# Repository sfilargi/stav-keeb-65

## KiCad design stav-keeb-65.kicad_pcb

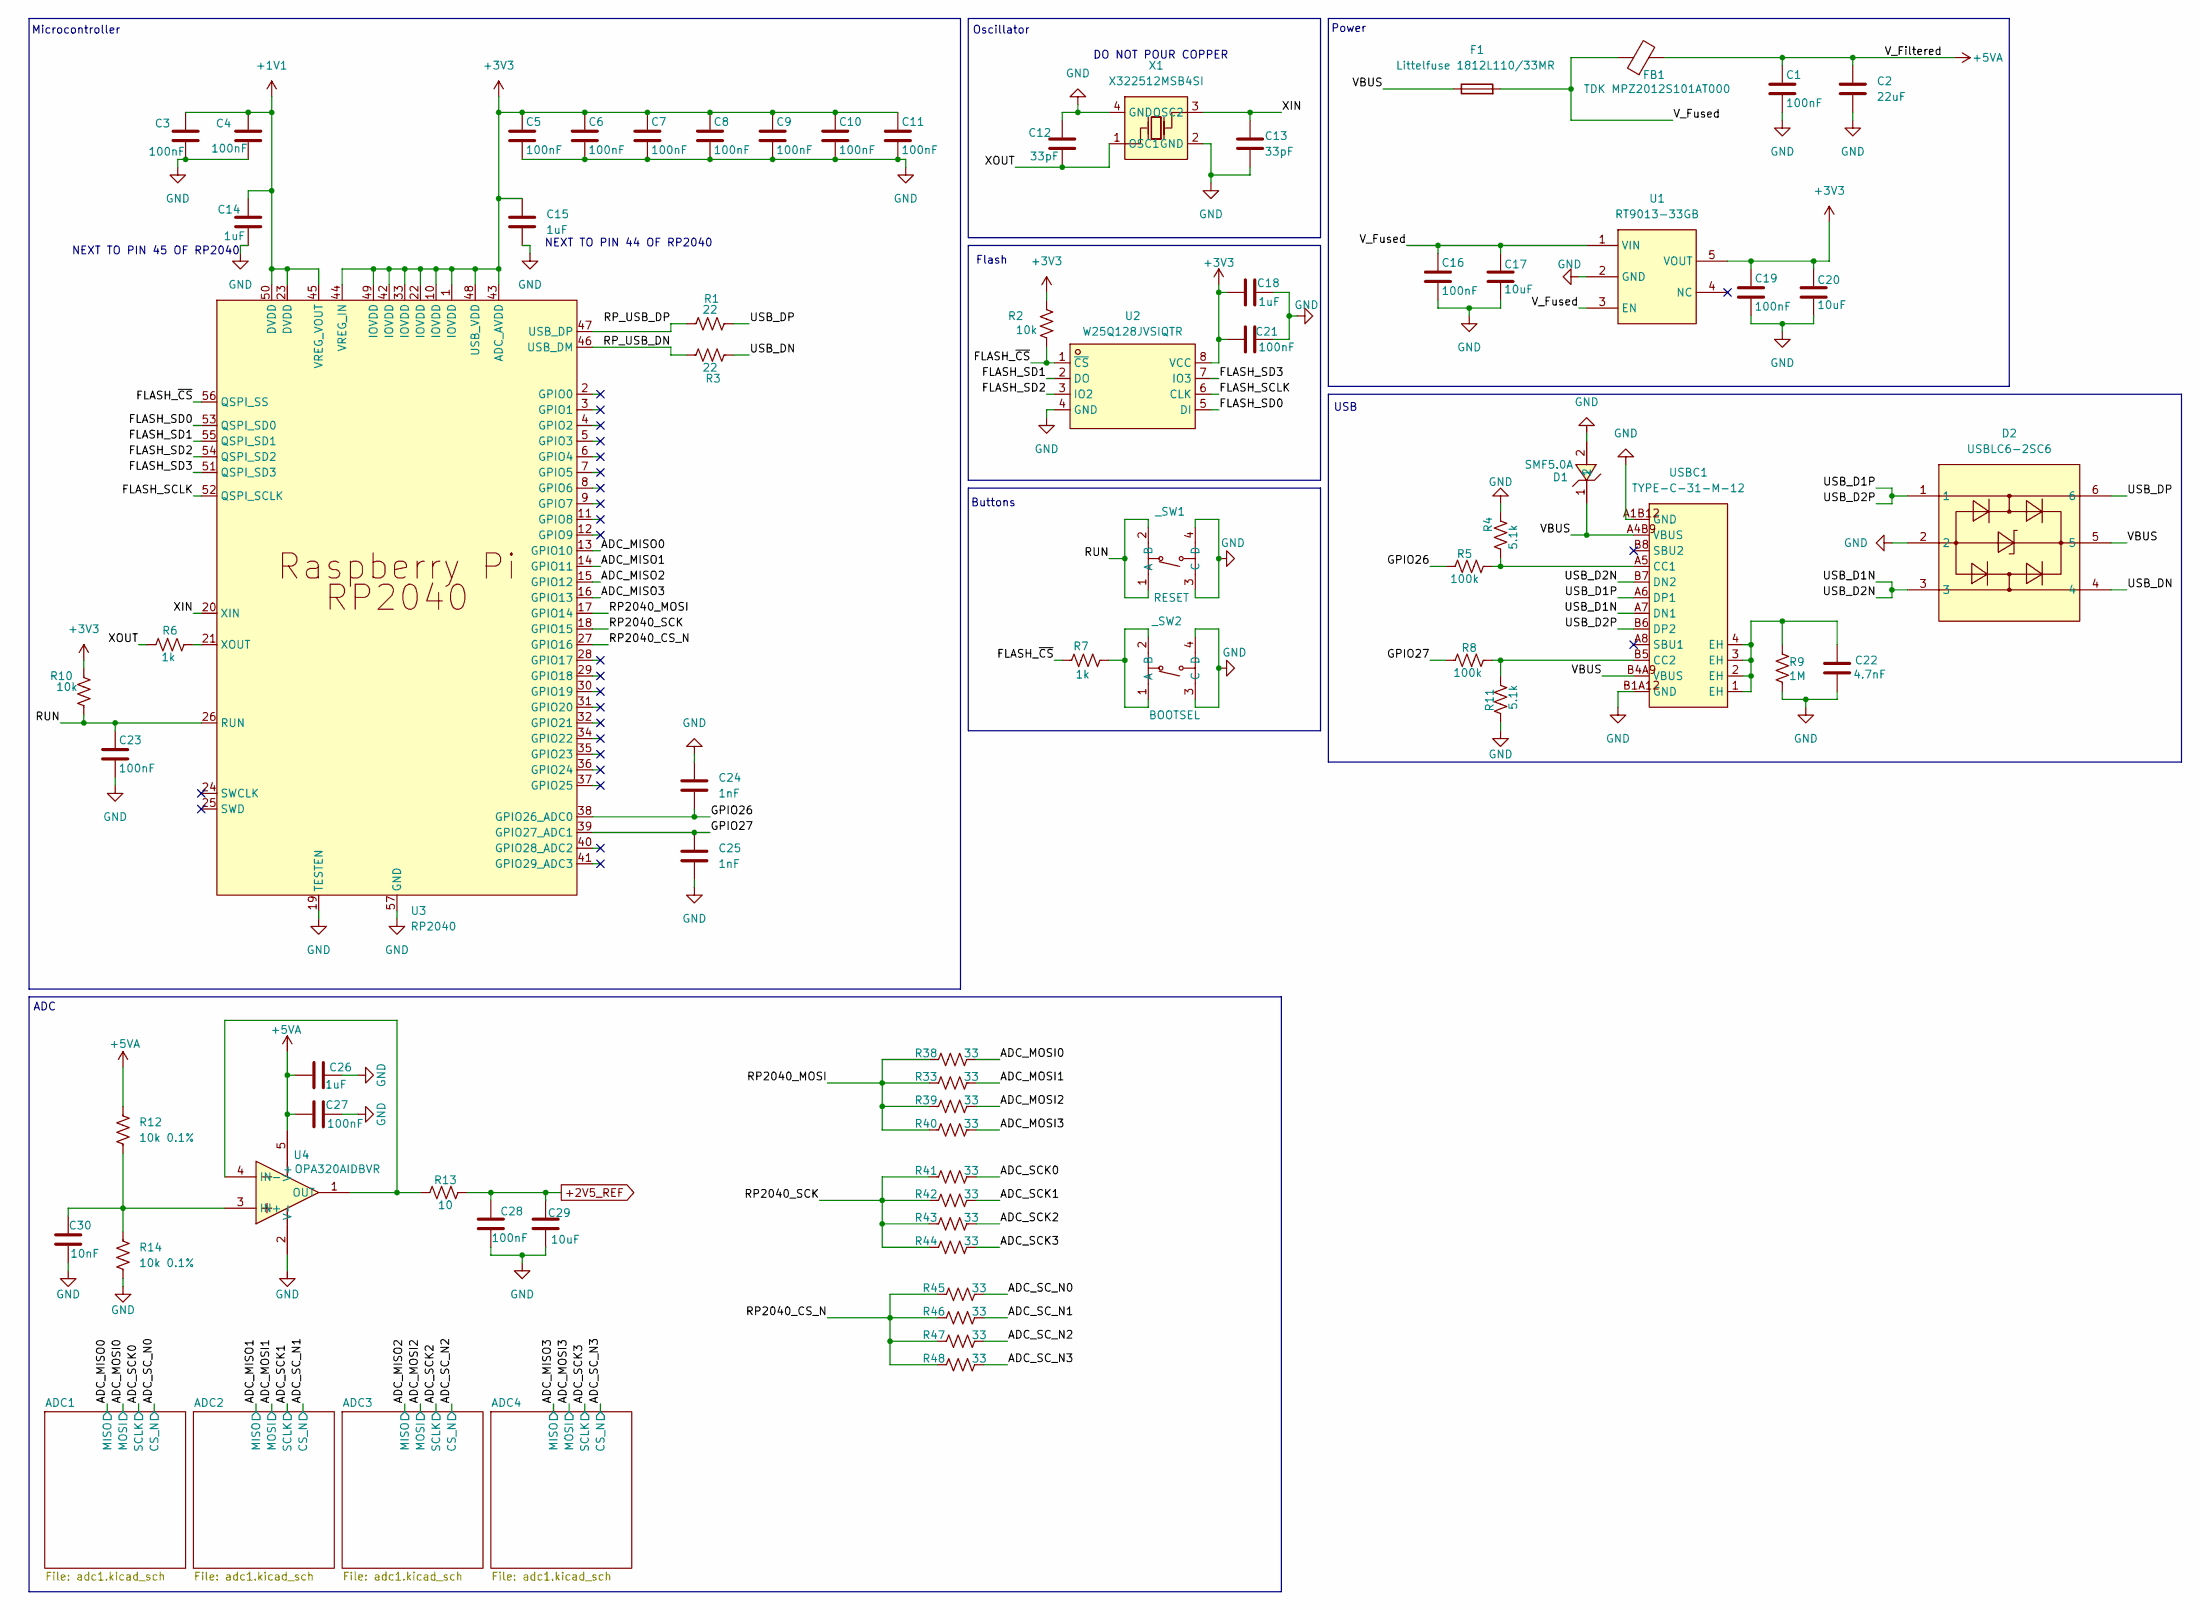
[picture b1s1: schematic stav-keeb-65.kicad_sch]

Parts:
C1, C16, C19: 100nF; C_1206_3216Metric; LCSC Part C14663
C2: 22uF; C_1206_3216Metric; LCSC Part C12891
C3, C4, C5, C6, C7, C8, C9, C10, C11, C21, C23, C27, C28: 100nF; C_0402_1005Metric; LCSC Part C14663
C12, C13: 33pF; C_0402_1005Metric; LCSC Part C1663
C14, C15, C18, C26: 1uF; C_0402_1005Metric; LCSC Part C15849
C17, C20: 10uF; C_1206_3216Metric; LCSC Part C13585
C22: 4.7nF; C_1206_3216Metric; LCSC Part C53987
C24, C25: 1nF; C_0402_1005Metric; LCSC Part C1588
C29: 10uF; C_1206_3216Metric_Pad1.33x1.80mm_HandSolder; LCSC Part C13585
C30: 10nF; C_0402_1005Metric; LCSC Part C57112
D1: SMF5.0A; SOD-123F_L2.8-W1.8-LS3.7-RD; MPN SMF5.0A; LCSC Part C151296
D2: USBLC6-2SC6; SOT-23-6_L2.9-W1.6-P0.95-LS2.8-BL; MPN USBLC6-2SC6; LCSC Part C7519
F1: Littelfuse 1812L110/33MR; Fuse_1812_4532Metric_Pad1.30x3.40mm_HandSolder; LCSC Part C142747
FB1: TDK MPZ2012S101AT000; L_0805_2012Metric_Pad1.05x1.20mm_HandSolder; LCSC Part C15957
R1, R3: 22; R_0402_1005Metric; LCSC Part C23345
R2, R10: 10k; R_0402_1005Metric; LCSC Part C25804
R4, R11: 5.1k; R_0402_1005Metric; LCSC Part C23186
R5, R8: 100k; R_0402_1005Metric; LCSC Part C25803
R6, R7: 1k; R_0402_1005Metric; LCSC Part C21190
R9: 1M; R_0402_1005Metric; LCSC Part C22935
R12, R14: 10k 0.1%; R_0603_1608Metric; LCSC Part C95204
R13: 10; R_0402_1005Metric; LCSC Part C22859
R33, R38, R39, R40, R41, R42, R43, R44, R45, R46, R47, R48: 33; R_0402_1005Metric; LCSC Part C23140
U1: RT9013-33GB; SOT-23-5_L3.0-W1.7-P0.95-LS2.8-BL; MPN RT9013-33GB; LCSC Part C47773
U2: W25Q128JVSIQTR; SOIC-8_L5.3-W5.3-P1.27-LS8.0-BL; MPN W25Q128JVSIQ; LCSC Part C97521
U3: RP2040; LQFN-56_L7.0-W7.0-P0.4-EP; MPN RP2040; LCSC Part C2040
U4: OPA320AIDBVR; SOT-23-5_L3.0-W1.7-P0.95-LS2.8-BR; MPN OPA320AIDBVR; LCSC Part C92494
USBC1: TYPE-C-31-M-12; USB-C_SMD-TYPE-C-31-M-12_1; MPN TYPE-C-31-M-12; LCSC Part C165948
X1: X322512MSB4SI; CRYSTAL-SMD_4P-L3.2-W2.5-BL; MPN X322512MSB4SI; LCSC Part C9002
_SW1: RESET; SW-SMD_4P-L5.1-W5.1-P3.70-LS6.5-TL_H1.5; MPN TS-1187A-B-A-B; LCSC Part C318884
_SW2: BOOTSEL; SW-SMD_4P-L5.1-W5.1-P3.70-LS6.5-TL_H1.5; MPN TS-1187A-B-A-B; LCSC Part C318884

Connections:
+1V1: C3.1, C4.1, C14.1, U3.23 (DVDD), U3.45 (VREG_VOUT), U3.50 (DVDD)
+2V5_REF: C28.2, C29.1, R13.2; also elsewhere on the board
+3V3: C5.1, C6.1, C7.1, C8.1, C9.1, C10.1, C11.1, C15.1, C18.2, C19.1, C20.1, C21.2, R2.1, R10.1, U1.5 (VOUT), U2.8 (VCC), U3.1 (IOVDD), U3.10 (IOVDD), U3.22 (IOVDD), U3.33 (IOVDD), U3.42 (IOVDD), U3.43 (ADC_AVDD), U3.44 (VREG_IN), U3.48 (USB_VDD), U3.49 (IOVDD); also elsewhere on the board
+5VA: C1.1, C2.1, C26.1, C27.2, FB1.2, R12.1, U4.5 (V+); also elsewhere on the board
/ADC_MISO0: U3.13 (GPIO10); also elsewhere on the board
/ADC_MISO1: U3.14 (GPIO11); also elsewhere on the board
/ADC_MISO2: U3.15 (GPIO12); also elsewhere on the board
/ADC_MISO3: U3.16 (GPIO13); also elsewhere on the board
/ADC_MOSI0: R38.2; also elsewhere on the board
/ADC_MOSI1: R33.2; also elsewhere on the board
/ADC_MOSI2: R39.2; also elsewhere on the board
/ADC_MOSI3: R40.2; also elsewhere on the board
/ADC_SCK0: R41.2; also elsewhere on the board
/ADC_SCK1: R42.2; also elsewhere on the board
/ADC_SCK2: R43.2; also elsewhere on the board
/ADC_SCK3: R44.2; also elsewhere on the board
/ADC_SC_N0: R45.2; also elsewhere on the board
/ADC_SC_N1: R46.2; also elsewhere on the board
/ADC_SC_N2: R47.2; also elsewhere on the board
/ADC_SC_N3: R48.2; also elsewhere on the board
/FLASH_SCLK: U2.6 (CLK), U3.52 (QSPI_SCLK)
/FLASH_SD0: U2.5 (DI), U3.53 (QSPI_SD0)
/FLASH_SD1: U2.2 (DO), U3.55 (QSPI_SD1)
/FLASH_SD2: U2.3 (IO2), U3.54 (QSPI_SD2)
/FLASH_SD3: U2.7 (IO3), U3.51 (QSPI_SD3)
/FLASH_~CS: R2.2, R7.1, U2.1 (~CS), U3.56 (QSPI_SS)
/GPIO26: C24.2, R5.1, U3.38 (GPIO26_ADC0)
/GPIO27: C25.1, R8.1, U3.39 (GPIO27_ADC1)
/RP2040_CS_N: R45.1, R46.1, R47.1, R48.1, U3.27 (GPIO16)
/RP2040_MOSI: R33.1, R38.1, R39.1, R40.1, U3.17 (GPIO14)
/RP2040_SCK: R41.1, R42.1, R43.1, R44.1, U3.18 (GPIO15)
/RP_USB_DN: R3.2, U3.46 (USB_DM)
/RP_USB_DP: R1.2, U3.47 (USB_DP)
/RUN: C23.1, R10.2, U3.26 (RUN), _SW1.1 (A), _SW1.2 (B)
/USB_D1N: D2.3, USBC1.A7 (DN1), USBC1.B7 (DN2)
/USB_D1P: D2.1, USBC1.A6 (DP1), USBC1.B6 (DP2)
/USB_DN: D2.4, R3.1
/USB_DP: D2.6, R1.1
/VBUS: D1.1, D2.5, F1.1, USBC1.A4B9 (VBUS), USBC1.B4A9 (VBUS)
/V_Fused: C16.1, C17.1, F1.2, FB1.1, U1.1 (VIN), U1.3 (EN)
/XIN: C13.1, U3.20 (XIN), X1.3 (OSC2)
/XOUT: C12.2, R6.1, X1.1 (OSC1)
GND: C1.2, C2.2, C3.2, C4.2, C5.2, C6.2, C7.2, C8.2, C9.2, C10.2, C11.2, C12.1, C13.2, C14.2, C15.2, C16.2, C17.2, C18.1, C19.2, C20.2, C21.1, C22.2, C23.2, C24.1, C25.2, C26.2, C27.1, C28.1, C29.2, C30.2, D1.2, D2.2, R4.2, R9.2, R11.2, R14.2, U1.2 (GND), U2.4 (GND), U3.19 (TESTEN), U3.57 (GND), U4.2 (V-), USBC1.A1B12 (GND), USBC1.B1A12 (GND), X1.2 (GND), X1.4 (GND), _SW1.3 (C), _SW1.4 (D), _SW2.3 (C), _SW2.4 (D); also elsewhere on the board
unnamed: C22.1, R9.1, USBC1.1 (EH), USBC1.2 (EH), USBC1.3 (EH), USBC1.4 (EH)
unnamed: R6.2, U3.21 (XOUT)
unnamed: C30.1, R12.2, R14.1, U4.3 (IN+)
unnamed: R13.1, U4.1 (OUT), U4.4 (IN-)
unnamed: R4.1, R5.2, USBC1.A5 (CC1)
unnamed: R8.2, R11.1, USBC1.B5 (CC2)
unnamed: R7.2, _SW2.1 (A), _SW2.2 (B)

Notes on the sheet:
Power
Oscillator
DO NOT POUR COPPER
Flash
NEXT TO PIN 45 OF RP2040
USB
ADC
Buttons
Microcontroller
NEXT TO PIN 44 OF RP2040

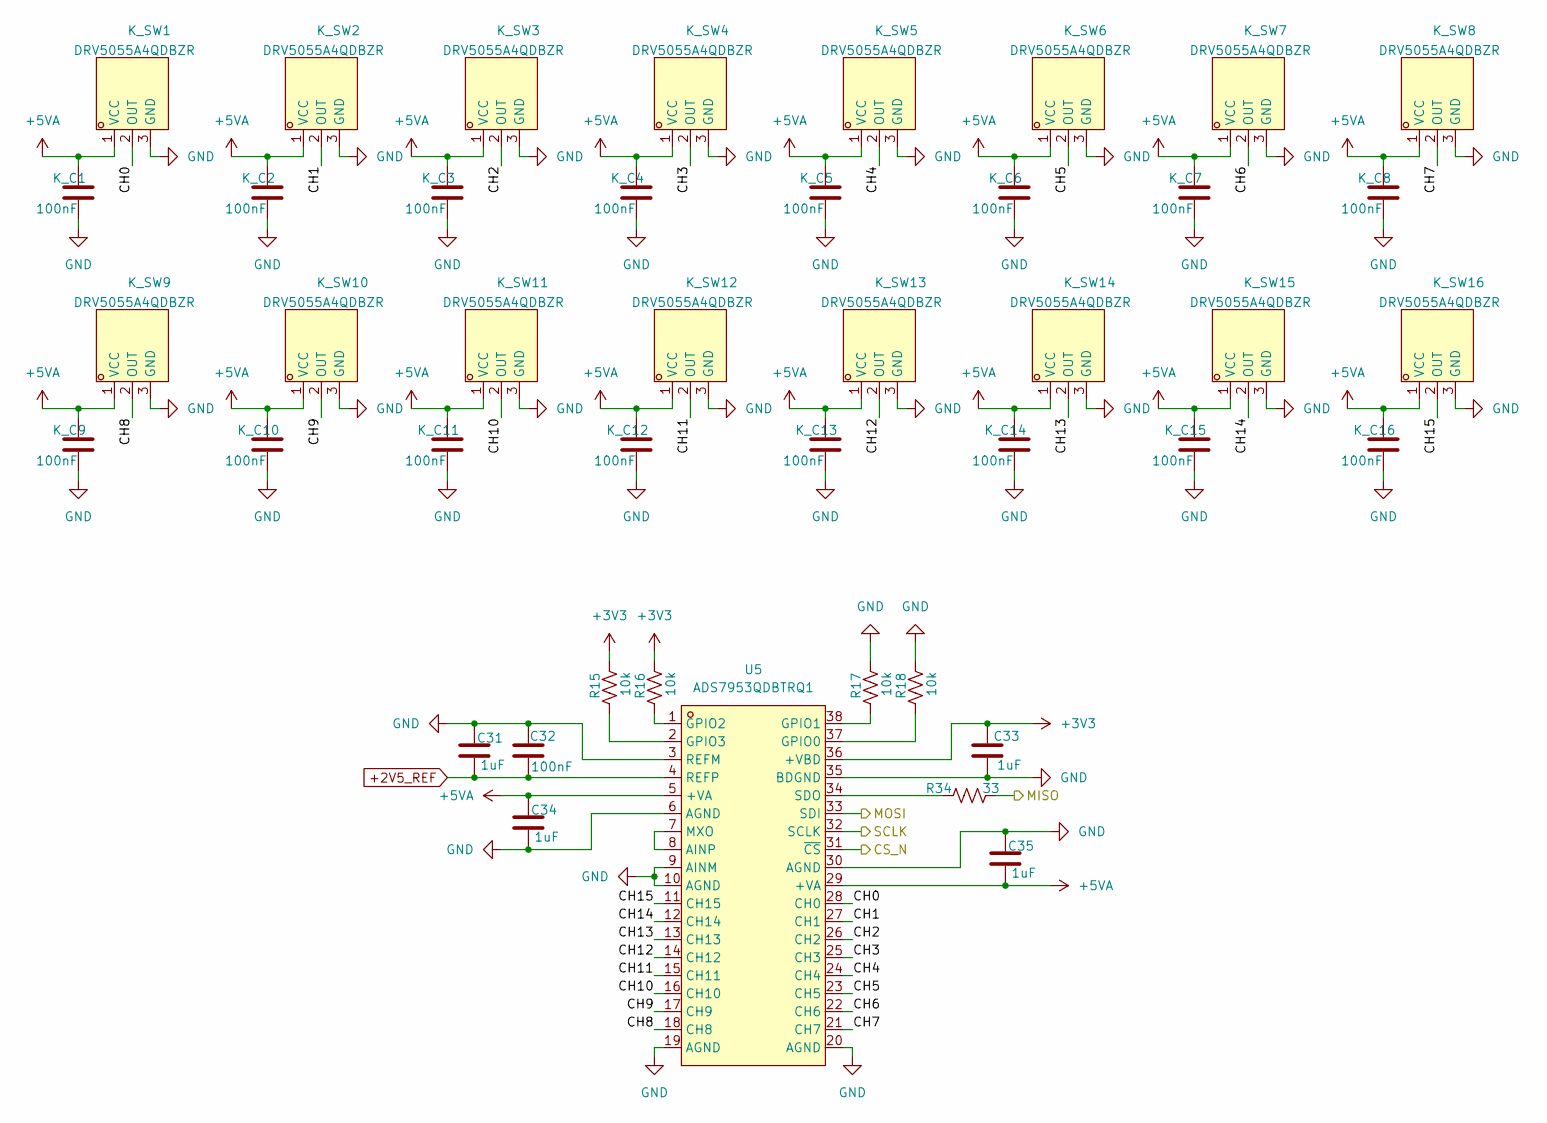
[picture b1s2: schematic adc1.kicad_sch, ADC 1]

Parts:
C31, C33, C34, C35: 1uF; C_0402_1005Metric; LCSC Part C15849
C32: 100nF; C_0402_1005Metric; LCSC Part C14663
K_C1, K_C2, K_C3, K_C4, K_C5, K_C6, K_C7, K_C8, K_C9, K_C10, K_C11, K_C12, K_C13, K_C14, K_C15, K_C16: 100nF; C_0402_1005Metric; LCSC Part C14663
K_SW1, K_SW2, K_SW3, K_SW4, K_SW5, K_SW6, K_SW7, K_SW8, K_SW9, K_SW10, K_SW11, K_SW12, K_SW13, K_SW14, K_SW15, K_SW16: DRV5055A4QDBZR; SOT-23-3_L2.9-W1.3-P1.90-LS2.4-BR; MPN DRV5055A4QDBZR; LCSC Part C266123
R15, R16, R17, R18: 10k; R_0402_1005Metric; LCSC Part C25804
R34: 33; R_0402_1005Metric; LCSC Part C23140
U5: ADS7953QDBTRQ1; TSSOP-38_L9.7-W4.4-P0.50-LS6.4-BL; MPN ADS7953QDBTRQ1; LCSC Part C701668

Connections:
+2V5_REF: C31.2, C32.1, U5.4 (REFP); also elsewhere on the board
+3V3: C33.1, R15.2, R16.2, U5.36 (+VBD); also elsewhere on the board
+5VA: C34.1, C35.2, K_C1.2, K_C2.2, K_C3.2, K_C4.2, K_C5.2, K_C6.2, K_C7.2, K_C8.2, K_C9.2, K_C10.2, K_C11.2, K_C12.2, K_C13.2, K_C14.2, K_C15.2, K_C16.2, K_SW1.1 (VCC), K_SW2.1 (VCC), K_SW3.1 (VCC), K_SW4.1 (VCC), K_SW5.1 (VCC), K_SW6.1 (VCC), K_SW7.1 (VCC), K_SW8.1 (VCC), K_SW9.1 (VCC), K_SW10.1 (VCC), K_SW11.1 (VCC), K_SW12.1 (VCC), K_SW13.1 (VCC), K_SW14.1 (VCC), K_SW15.1 (VCC), K_SW16.1 (VCC), U5.5 (+VA), U5.29 (+VA); also elsewhere on the board
/ADC1/CH0: K_SW1.2 (OUT), U5.28 (CH0)
/ADC1/CH1: K_SW2.2 (OUT), U5.27 (CH1)
/ADC1/CH2: K_SW3.2 (OUT), U5.26 (CH2)
/ADC1/CH3: K_SW4.2 (OUT), U5.25 (CH3)
/ADC1/CH4: K_SW5.2 (OUT), U5.24 (CH4)
/ADC1/CH5: K_SW6.2 (OUT), U5.23 (CH5)
/ADC1/CH6: K_SW7.2 (OUT), U5.22 (CH6)
/ADC1/CH7: K_SW8.2 (OUT), U5.21 (CH7)
/ADC1/CH8: K_SW9.2 (OUT), U5.18 (CH8)
/ADC1/CH9: K_SW10.2 (OUT), U5.17 (CH9)
/ADC1/CH10: K_SW11.2 (OUT), U5.16 (CH10)
/ADC1/CH11: K_SW12.2 (OUT), U5.15 (CH11)
/ADC1/CH12: K_SW13.2 (OUT), U5.14 (CH12)
/ADC1/CH13: K_SW14.2 (OUT), U5.13 (CH13)
/ADC1/CH14: K_SW15.2 (OUT), U5.12 (CH14)
/ADC1/CH15: K_SW16.2 (OUT), U5.11 (CH15)
/ADC_MISO0: R34.2; also elsewhere on the board
/ADC_MOSI0: U5.33 (SDI); also elsewhere on the board
/ADC_SCK0: U5.32 (SCLK); also elsewhere on the board
/ADC_SC_N0: U5.31 (~CS); also elsewhere on the board
GND: C31.1, C32.2, C33.2, C34.2, C35.1, K_C1.1, K_C2.1, K_C3.1, K_C4.1, K_C5.1, K_C6.1, K_C7.1, K_C8.1, K_C9.1, K_C10.1, K_C11.1, K_C12.1, K_C13.1, K_C14.1, K_C15.1, K_C16.1, K_SW1.3 (GND), K_SW2.3 (GND), K_SW3.3 (GND), K_SW4.3 (GND), K_SW5.3 (GND), K_SW6.3 (GND), K_SW7.3 (GND), K_SW8.3 (GND), K_SW9.3 (GND), K_SW10.3 (GND), K_SW11.3 (GND), K_SW12.3 (GND), K_SW13.3 (GND), K_SW14.3 (GND), K_SW15.3 (GND), K_SW16.3 (GND), R17.2, R18.2, U5.3 (REFM), U5.6 (AGND), U5.9 (AINM), U5.10 (AGND), U5.19 (AGND), U5.20 (AGND), U5.30 (AGND), U5.35 (BDGND); also elsewhere on the board
unnamed: U5.7 (MXO), U5.8 (AINP)
unnamed: R18.1, U5.37 (GPIO0)
unnamed: R17.1, U5.38 (GPIO1)
unnamed: R16.1, U5.1 (GPIO2)
unnamed: R15.1, U5.2 (GPIO3)
unnamed: R34.1, U5.34 (SDO)

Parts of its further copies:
C36, C38, C39, C40, C41, C43, C44, C45, C46, C48, C49, C50: 1uF; C_0402_1005Metric; LCSC Part C15849
C37, C42, C47: 100nF; C_0402_1005Metric; LCSC Part C14663
K_C17, K_C18, K_C19, K_C20, K_C21, K_C22, K_C23, K_C24, K_C25, K_C26, K_C27, K_C28, K_C29, K_C30, K_C31, K_C32, K_C33, K_C34, K_C35, K_C36, K_C37, K_C38, K_C39, K_C40, K_C41, K_C42, K_C43, K_C44, K_C45, K_C46, K_C47, K_C48, K_C49, K_C50, K_C51, K_C52, K_C53, K_C54, K_C55, K_C56, K_C57, K_C58, K_C59, K_C60, K_C61: 100nF; C_0402_1005Metric; LCSC Part C14663
K_SW17, K_SW18, K_SW19, K_SW20, K_SW21, K_SW22, K_SW23, K_SW24, K_SW25, K_SW26, K_SW27, K_SW28, K_SW29, K_SW30, K_SW31, K_SW32, K_SW33, K_SW34, K_SW35, K_SW36, K_SW37, K_SW38, K_SW39, K_SW40, K_SW41, K_SW42, K_SW43, K_SW44, K_SW45, K_SW46, K_SW47, K_SW48, K_SW49, K_SW50, K_SW51, K_SW52, K_SW53, K_SW54, K_SW55, K_SW56, K_SW57, K_SW58, K_SW59, K_SW60, K_SW61: DRV5055A4QDBZR; SOT-23-3_L2.9-W1.3-P1.90-LS2.4-BR; MPN DRV5055A4QDBZR; LCSC Part C266123
R19, R20, R21, R22, R23, R24, R25, R26, R27, R28, R29, R30: 10k; R_0402_1005Metric; LCSC Part C25804
R35, R36, R37: 33; R_0402_1005Metric; LCSC Part C23140
U6, U7, U8: ADS7953QDBTRQ1; TSSOP-38_L9.7-W4.4-P0.50-LS6.4-BL; MPN ADS7953QDBTRQ1; LCSC Part C701668

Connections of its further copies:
+2V5_REF: C36.2, C37.1, C41.2, C42.1, C46.2, C47.1, U6.4 (REFP), U7.4 (REFP), U8.4 (REFP); also elsewhere on the board
+3V3: C38.1, C43.1, C48.1, R19.2, R20.2, R23.2, R24.2, R27.2, R28.2, U6.36 (+VBD), U7.36 (+VBD), U8.36 (+VBD); also elsewhere on the board
+5VA: C39.1, C40.2, C44.1, C45.2, C49.1, C50.2, K_C17.2, K_C18.2, K_C19.2, K_C20.2, K_C21.2, K_C22.2, K_C23.2, K_C24.2, K_C25.2, K_C26.2, K_C27.2, K_C28.2, K_C29.2, K_C30.2, K_C31.2, K_C32.2, K_C33.2, K_C34.2, K_C35.2, K_C36.2, K_C37.2, K_C38.2, K_C39.2, K_C40.2, K_C41.2, K_C42.2, K_C43.2, K_C44.2, K_C45.2, K_C46.2, K_C47.2, K_C48.2, K_C49.2, K_C50.2, K_C51.2, K_C52.2, K_C53.2, K_C54.2, K_C55.2, K_C56.2, K_C57.2, K_C58.2, K_C59.2, K_C60.2, K_C61.2, K_SW17.1 (VCC), K_SW18.1 (VCC), K_SW19.1 (VCC), K_SW20.1 (VCC), K_SW21.1 (VCC), K_SW22.1 (VCC), K_SW23.1 (VCC), K_SW24.1 (VCC), K_SW25.1 (VCC), K_SW26.1 (VCC), K_SW27.1 (VCC), K_SW28.1 (VCC), K_SW29.1 (VCC), K_SW30.1 (VCC), K_SW31.1 (VCC), K_SW32.1 (VCC), K_SW33.1 (VCC), K_SW34.1 (VCC), K_SW35.1 (VCC), K_SW36.1 (VCC), K_SW37.1 (VCC), K_SW38.1 (VCC), K_SW39.1 (VCC), K_SW40.1 (VCC), K_SW41.1 (VCC), K_SW42.1 (VCC), K_SW43.1 (VCC), K_SW44.1 (VCC), K_SW45.1 (VCC), K_SW46.1 (VCC), K_SW47.1 (VCC), K_SW48.1 (VCC), K_SW49.1 (VCC), K_SW50.1 (VCC), K_SW51.1 (VCC), K_SW52.1 (VCC), K_SW53.1 (VCC), K_SW54.1 (VCC), K_SW55.1 (VCC), K_SW56.1 (VCC), K_SW57.1 (VCC), K_SW58.1 (VCC), K_SW59.1 (VCC), K_SW60.1 (VCC), K_SW61.1 (VCC), U6.5 (+VA), U6.29 (+VA), U7.5 (+VA), U7.29 (+VA), U8.5 (+VA), U8.29 (+VA); also elsewhere on the board
/ADC2/CH0: K_SW17.2 (OUT), U6.28 (CH0)
/ADC2/CH1: K_SW18.2 (OUT), U6.27 (CH1)
/ADC2/CH2: K_SW19.2 (OUT), U6.26 (CH2)
/ADC2/CH3: K_SW20.2 (OUT), U6.25 (CH3)
/ADC2/CH4: K_SW21.2 (OUT), U6.24 (CH4)
/ADC2/CH5: K_SW22.2 (OUT), U6.23 (CH5)
/ADC2/CH6: K_SW23.2 (OUT), U6.22 (CH6)
/ADC2/CH7: K_SW24.2 (OUT), U6.21 (CH7)
/ADC2/CH8: K_SW25.2 (OUT), U6.18 (CH8)
/ADC2/CH9: K_SW26.2 (OUT), U6.17 (CH9)
/ADC2/CH10: K_SW27.2 (OUT), U6.16 (CH10)
/ADC2/CH11: K_SW28.2 (OUT), U6.15 (CH11)
/ADC2/CH12: K_SW29.2 (OUT), U6.14 (CH12)
/ADC2/CH13: K_SW30.2 (OUT), U6.13 (CH13)
/ADC2/CH14: K_SW31.2 (OUT), U6.12 (CH14)
/ADC2/CH15: K_SW32.2 (OUT), U6.11 (CH15)
/ADC3/CH0: K_SW33.2 (OUT), U7.28 (CH0)
/ADC3/CH1: K_SW34.2 (OUT), U7.27 (CH1)
/ADC3/CH2: K_SW35.2 (OUT), U7.26 (CH2)
/ADC3/CH3: K_SW36.2 (OUT), U7.25 (CH3)
/ADC3/CH4: K_SW37.2 (OUT), U7.24 (CH4)
/ADC3/CH5: K_SW38.2 (OUT), U7.23 (CH5)
/ADC3/CH6: K_SW39.2 (OUT), U7.22 (CH6)
/ADC3/CH7: K_SW40.2 (OUT), U7.21 (CH7)
/ADC3/CH8: K_SW41.2 (OUT), U7.18 (CH8)
/ADC3/CH9: K_SW42.2 (OUT), U7.17 (CH9)
/ADC3/CH10: K_SW43.2 (OUT), U7.16 (CH10)
/ADC3/CH11: K_SW44.2 (OUT), U7.15 (CH11)
/ADC3/CH12: K_SW45.2 (OUT), U7.14 (CH12)
/ADC3/CH13: K_SW46.2 (OUT), U7.13 (CH13)
/ADC3/CH14: K_SW47.2 (OUT), U7.12 (CH14)
/ADC3/CH15: K_SW48.2 (OUT), U7.11 (CH15)
/ADC4/CH0: K_SW49.2 (OUT), U8.28 (CH0)
/ADC4/CH1: K_SW50.2 (OUT), U8.27 (CH1)
/ADC4/CH2: K_SW51.2 (OUT), U8.26 (CH2)
/ADC4/CH3: K_SW52.2 (OUT), U8.25 (CH3)
/ADC4/CH4: K_SW53.2 (OUT), U8.24 (CH4)
/ADC4/CH5: K_SW54.2 (OUT), U8.23 (CH5)
/ADC4/CH6: K_SW55.2 (OUT), U8.22 (CH6)
/ADC4/CH7: K_SW56.2 (OUT), U8.21 (CH7)
/ADC4/CH8: K_SW57.2 (OUT), U8.18 (CH8)
/ADC4/CH9: K_SW58.2 (OUT), U8.17 (CH9)
/ADC4/CH10: K_SW59.2 (OUT), U8.16 (CH10)
/ADC4/CH11: K_SW60.2 (OUT), U8.15 (CH11)
/ADC4/CH12: K_SW61.2 (OUT), U8.14 (CH12)
/ADC4/CH13: U8.13 (CH13)
/ADC4/CH14: U8.12 (CH14)
/ADC4/CH15: U8.11 (CH15)
/ADC_MISO1: R35.2; also elsewhere on the board
/ADC_MISO2: R36.2; also elsewhere on the board
/ADC_MISO3: R37.2; also elsewhere on the board
/ADC_MOSI1: U6.33 (SDI); also elsewhere on the board
/ADC_MOSI2: U7.33 (SDI); also elsewhere on the board
/ADC_MOSI3: U8.33 (SDI); also elsewhere on the board
/ADC_SCK1: U6.32 (SCLK); also elsewhere on the board
/ADC_SCK2: U7.32 (SCLK); also elsewhere on the board
/ADC_SCK3: U8.32 (SCLK); also elsewhere on the board
/ADC_SC_N1: U6.31 (~CS); also elsewhere on the board
/ADC_SC_N2: U7.31 (~CS); also elsewhere on the board
/ADC_SC_N3: U8.31 (~CS); also elsewhere on the board
GND: C36.1, C37.2, C38.2, C39.2, C40.1, C41.1, C42.2, C43.2, C44.2, C45.1, C46.1, C47.2, C48.2, C49.2, C50.1, K_C17.1, K_C18.1, K_C19.1, K_C20.1, K_C21.1, K_C22.1, K_C23.1, K_C24.1, K_C25.1, K_C26.1, K_C27.1, K_C28.1, K_C29.1, K_C30.1, K_C31.1, K_C32.1, K_C33.1, K_C34.1, K_C35.1, K_C36.1, K_C37.1, K_C38.1, K_C39.1, K_C40.1, K_C41.1, K_C42.1, K_C43.1, K_C44.1, K_C45.1, K_C46.1, K_C47.1, K_C48.1, K_C49.1, K_C50.1, K_C51.1, K_C52.1, K_C53.1, K_C54.1, K_C55.1, K_C56.1, K_C57.1, K_C58.1, K_C59.1, K_C60.1, K_C61.1, K_SW17.3 (GND), K_SW18.3 (GND), K_SW19.3 (GND), K_SW20.3 (GND), K_SW21.3 (GND), K_SW22.3 (GND), K_SW23.3 (GND), K_SW24.3 (GND), K_SW25.3 (GND), K_SW26.3 (GND), K_SW27.3 (GND), K_SW28.3 (GND), K_SW29.3 (GND), K_SW30.3 (GND), K_SW31.3 (GND), K_SW32.3 (GND), K_SW33.3 (GND), K_SW34.3 (GND), K_SW35.3 (GND), K_SW36.3 (GND), K_SW37.3 (GND), K_SW38.3 (GND), K_SW39.3 (GND), K_SW40.3 (GND), K_SW41.3 (GND), K_SW42.3 (GND), K_SW43.3 (GND), K_SW44.3 (GND), K_SW45.3 (GND), K_SW46.3 (GND), K_SW47.3 (GND), K_SW48.3 (GND), K_SW49.3 (GND), K_SW50.3 (GND), K_SW51.3 (GND), K_SW52.3 (GND), K_SW53.3 (GND), K_SW54.3 (GND), K_SW55.3 (GND), K_SW56.3 (GND), K_SW57.3 (GND), K_SW58.3 (GND), K_SW59.3 (GND), K_SW60.3 (GND), K_SW61.3 (GND), R21.2, R22.2, R25.2, R26.2, R29.2, R30.2, U6.3 (REFM), U6.6 (AGND), U6.9 (AINM), U6.10 (AGND), U6.19 (AGND), U6.20 (AGND), U6.30 (AGND), U6.35 (BDGND), U7.3 (REFM), U7.6 (AGND), U7.9 (AINM), U7.10 (AGND), U7.19 (AGND), U7.20 (AGND), U7.30 (AGND), U7.35 (BDGND), U8.3 (REFM), U8.6 (AGND), U8.9 (AINM), U8.10 (AGND), U8.19 (AGND), U8.20 (AGND), U8.30 (AGND), U8.35 (BDGND); also elsewhere on the board
unnamed: U6.7 (MXO), U6.8 (AINP)
unnamed: R22.1, U6.37 (GPIO0)
unnamed: R21.1, U6.38 (GPIO1)
unnamed: R20.1, U6.1 (GPIO2)
unnamed: R19.1, U6.2 (GPIO3)
unnamed: R35.1, U6.34 (SDO)
unnamed: U7.7 (MXO), U7.8 (AINP)
unnamed: R26.1, U7.37 (GPIO0)
unnamed: R25.1, U7.38 (GPIO1)
unnamed: R24.1, U7.1 (GPIO2)
unnamed: R23.1, U7.2 (GPIO3)
unnamed: R36.1, U7.34 (SDO)
unnamed: U8.7 (MXO), U8.8 (AINP)
unnamed: R30.1, U8.37 (GPIO0)
unnamed: R29.1, U8.38 (GPIO1)
unnamed: R28.1, U8.1 (GPIO2)
unnamed: R27.1, U8.2 (GPIO3)
unnamed: R37.1, U8.34 (SDO)

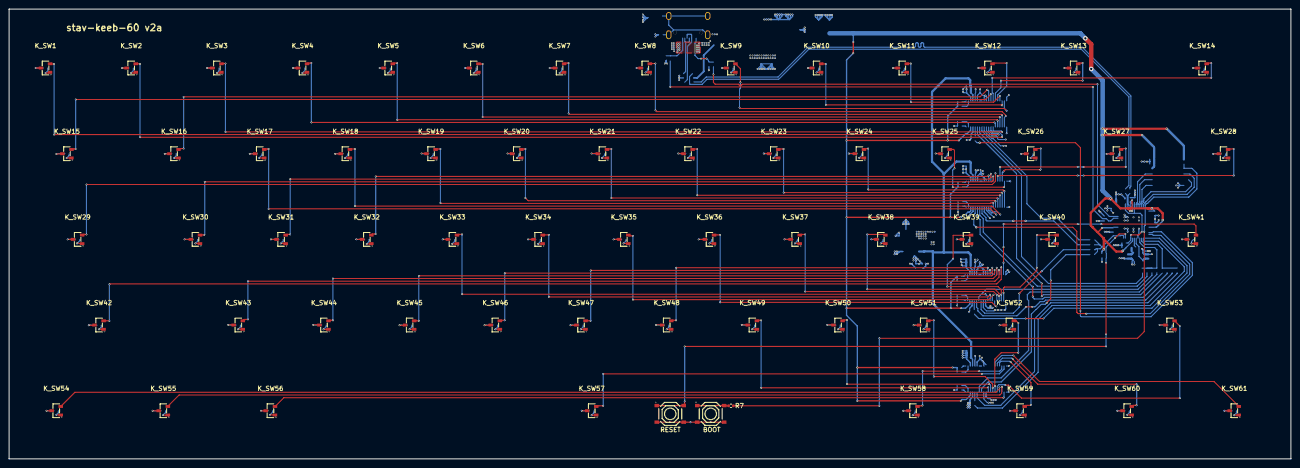
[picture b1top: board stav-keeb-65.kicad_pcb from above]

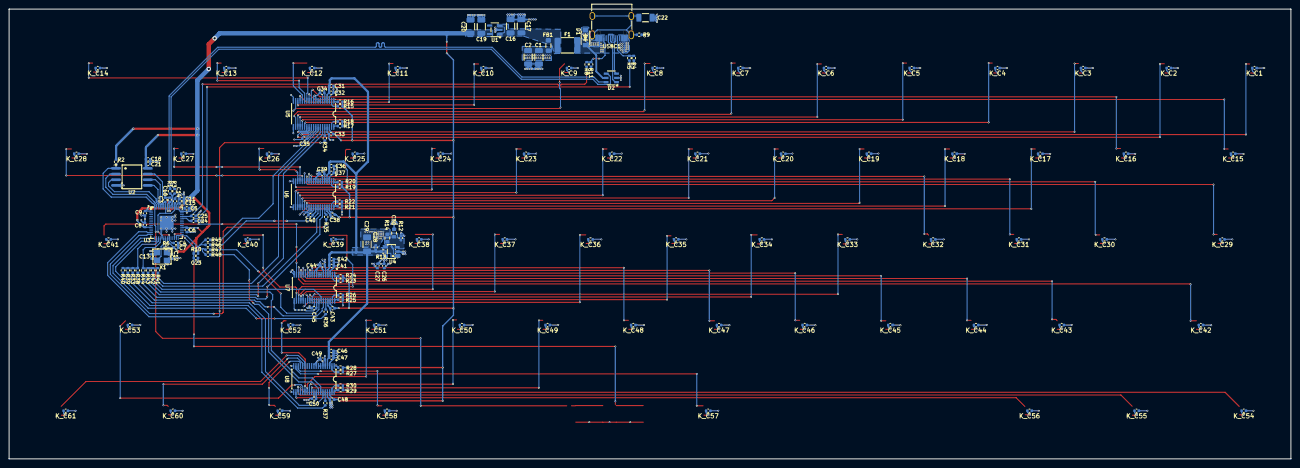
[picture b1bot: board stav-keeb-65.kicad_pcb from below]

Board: 4 copper layers, 285.0 x 100.0 mm, 234 parts (170 on the bottom side), 135 nets.
